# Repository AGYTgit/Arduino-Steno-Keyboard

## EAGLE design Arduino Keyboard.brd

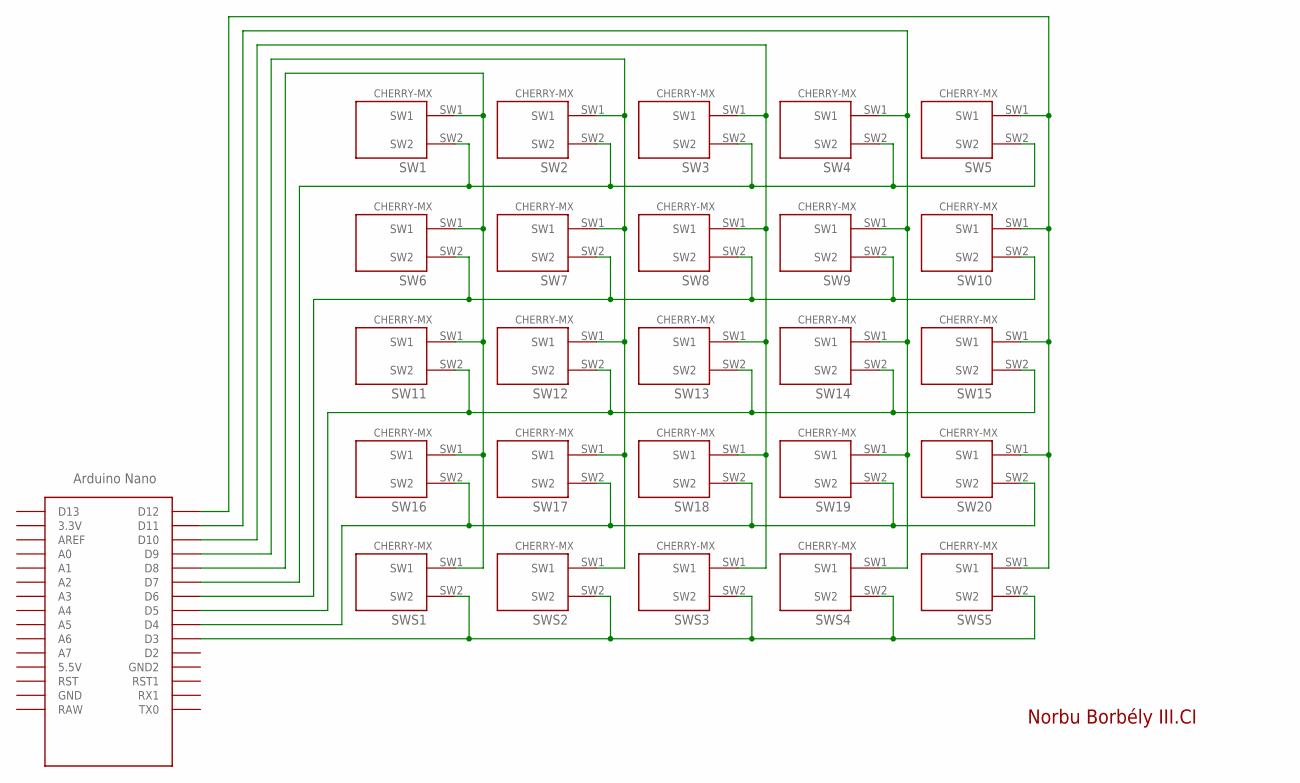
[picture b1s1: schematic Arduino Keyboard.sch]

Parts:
SW1, SW2, SW3, SW4, SW5, SW6, SW7, SW8, SW9, SW10, SW11, SW12, SW13, SW14, SW15, SW16, SW17, SW18, SW19, SW20: CHERRY-MXSTANDARD; CHERRY-MX
SWS1, SWS2, SWS3, SWS4, SWS5: CHERRY-MXSTANDARD; CHERRY-MX
U$1: NANO

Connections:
unnamed: SWS1.SW2, SWS2.SW2, SWS3.SW2, SWS4.SW2, SWS5.SW2, U$1.D3
unnamed: SW16.SW2, SW17.SW2, SW18.SW2, SW19.SW2, SW20.SW2, U$1.D4
unnamed: SW11.SW2, SW12.SW2, SW13.SW2, SW14.SW2, SW15.SW2, U$1.D5
unnamed: SW6.SW2, SW7.SW2, SW8.SW2, SW9.SW2, SW10.SW2, U$1.D6
unnamed: SW1.SW2, SW2.SW2, SW3.SW2, SW4.SW2, SW5.SW2, U$1.D7
unnamed: SW1.SW1, SW6.SW1, SW11.SW1, SW16.SW1, SWS1.SW1, U$1.D8
unnamed: SW2.SW1, SW7.SW1, SW12.SW1, SW17.SW1, SWS2.SW1, U$1.D9
unnamed: SW3.SW1, SW8.SW1, SW13.SW1, SW18.SW1, SWS3.SW1, U$1.D10
unnamed: SW4.SW1, SW9.SW1, SW14.SW1, SW19.SW1, SWS4.SW1, U$1.D11
unnamed: SW5.SW1, SW10.SW1, SW15.SW1, SW20.SW1, SWS5.SW1, U$1.D12

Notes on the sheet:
Norbu Borbély III.CI

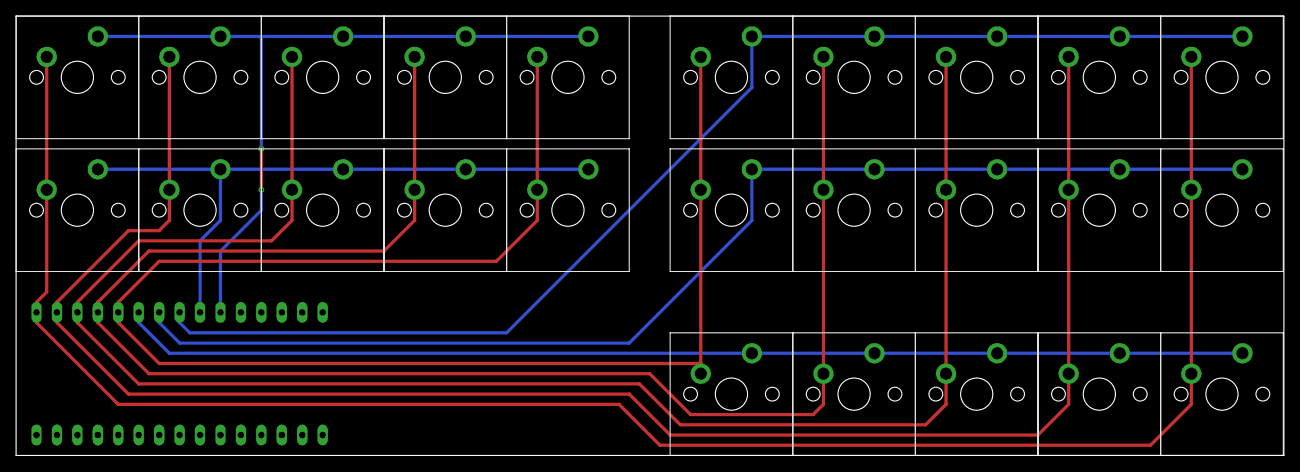
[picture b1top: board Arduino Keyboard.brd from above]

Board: 2 copper layers, 157.6 x 54.6 mm, 26 parts (0 on the bottom side), 10 nets.

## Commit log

2024-05-27 Version 0.1
2024-06-04 Version 0.2
2024-06-11 Version 0.3
2024-06-16 Version 0.4
